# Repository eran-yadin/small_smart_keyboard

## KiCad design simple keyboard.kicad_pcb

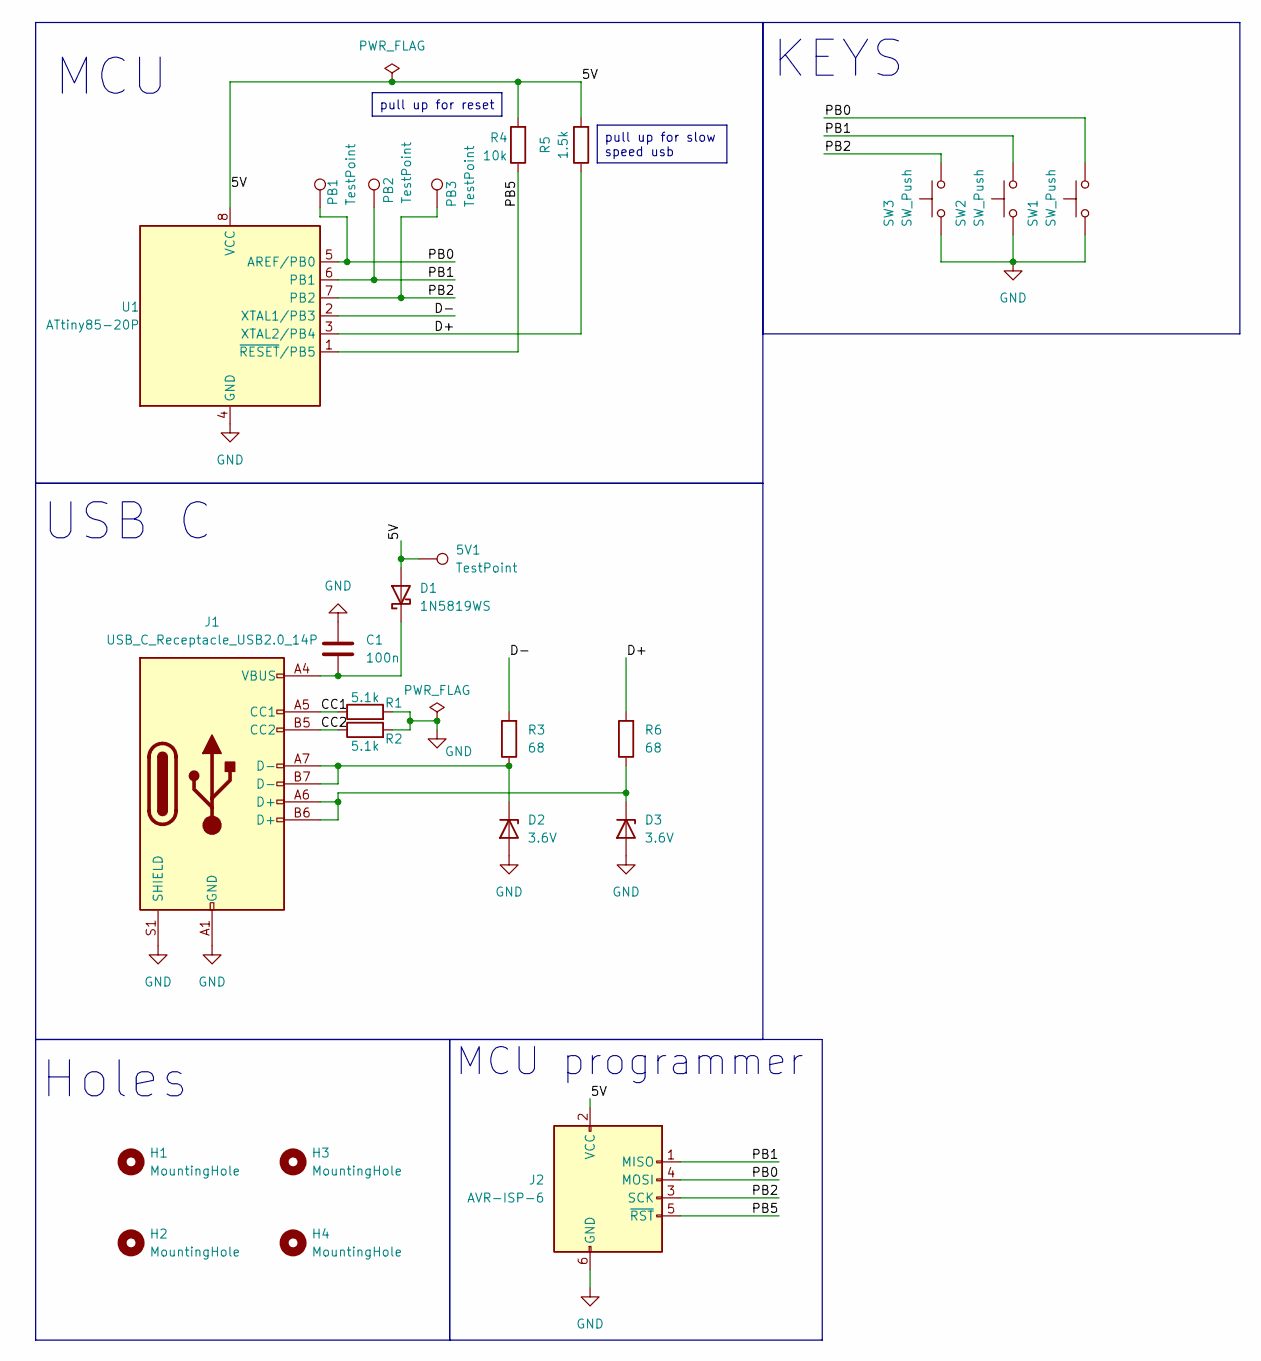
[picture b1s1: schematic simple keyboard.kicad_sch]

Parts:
5V1: TestPoint; TestPoint_Pad_1.0x1.0mm
C1: 100n; CP_EIA-6032-28_Kemet-C; Part_num 293D107X0010C2WE3
D1: 1N5819WS; D_SOD-323; Part_num 1N5819WS
D2, D3: 3.6V; D_DO-35_SOD27_P7.62mm_Horizontal; Part_num TZX3V6C-TR
H1, H2, H3, H4: MountingHole; MountingHole_2.1mm
J1: USB_C_Receptacle_USB2.0_14P; USB_C_Receptacle_GCT_USB4085; Part_num UJ20-C-H-G-TH-P16-TR
J2: AVR-ISP-6; 665306124022; Part_num 665306124022
PB1, PB2, PB3: TestPoint; TestPoint_Pad_D1.0mm
R1, R2: 5.1k; R_Axial_DIN0204_L3.6mm_D1.6mm_P5.08mm_Horizontal; Part_num MFR-12FTF52-5K1
R3, R6: 68; R_Axial_DIN0204_L3.6mm_D1.6mm_P5.08mm_Horizontal; Part_num MFR25SFTF52-68R
R4: 10k; R_Axial_DIN0204_L3.6mm_D1.6mm_P5.08mm_Horizontal; Part_num MFR25SFRF52-10K
R5: 1.5k; R_Axial_DIN0207_L6.3mm_D2.5mm_P7.62mm_Horizontal; Part_num MFR50SFTE52-1K
SW1, SW2, SW3: SW_Push; SW_Cherry_MX_1.00u_PCB
U1: ATtiny85-20P; DIP-8_W7.62mm

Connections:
/5V: 5V1.1, D1.2 (A), J2.2 (VCC), R4.2, R5.2, U1.8 (VCC)
/CC1: J1.A5 (CC1), R1.1
/CC2: J1.B5 (CC2), R2.1
/D+: R5.1, R6.2, U1.3 (XTAL2/PB4)
/D-: R3.2, U1.2 (XTAL1/PB3)
/PB0: J2.4 (MOSI), PB1.1, SW1.2, U1.5 (AREF/PB0)
/PB1: J2.1 (MISO), PB2.1, SW2.2, U1.6 (PB1)
/PB2: J2.3 (SCK), PB3.1, SW3.2, U1.7 (PB2)
/PB5: J2.5 (~RST), R4.1, U1.1 (~RESET/PB5)
GND: C1.1, D2.2 (A), D3.2 (A), J1.A1 (GND), J1.A12 (GND), J1.B1 (GND), J1.B12 (GND), J1.S1 (SHIELD), J2.6 (GND), R1.2, R2.2, SW1.1, SW2.1, SW3.1, U1.4 (GND)
unnamed: C1.2, D1.1 (K), J1.A4 (VBUS), J1.A9 (VBUS), J1.B4 (VBUS), J1.B9 (VBUS)
unnamed: D2.1 (K), J1.A7 (D-), J1.B7 (D-), R3.1
unnamed: D3.1 (K), J1.A6 (D+), J1.B6 (D+), R6.1

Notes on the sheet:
USB C
KEYS
MCU programmer
Holes
MCU
pull up for reset
pull up for slow speed usb

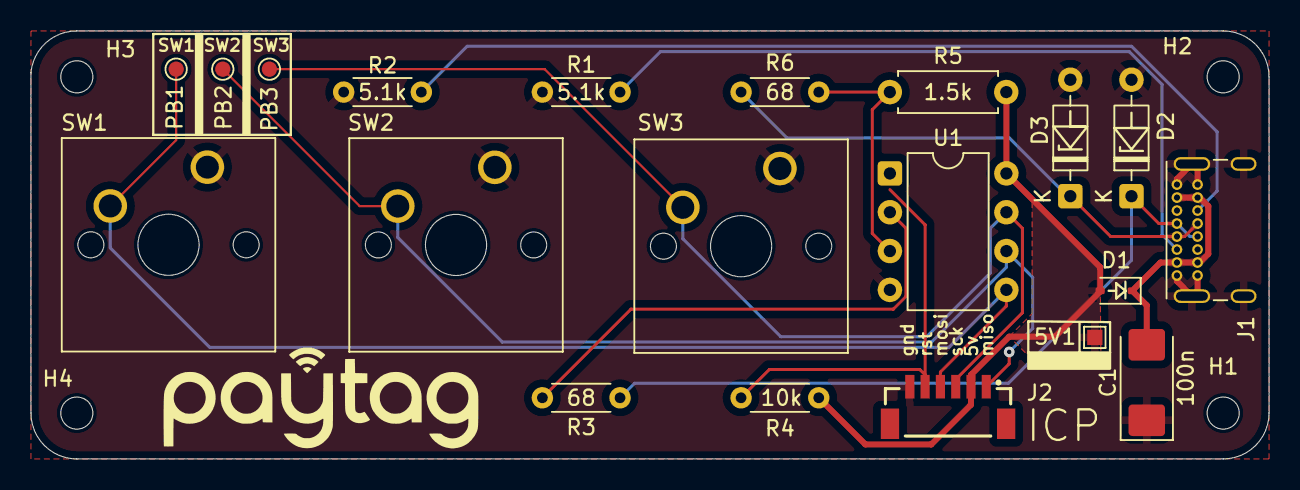
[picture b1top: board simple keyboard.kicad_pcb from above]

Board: 2 copper layers, 81.0 x 28.0 mm, 24 parts (0 on the bottom side), 13 nets.

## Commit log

2026-03-18 base model
2026-03-29 gitignore
2026-03-29 updata 29 3 26
